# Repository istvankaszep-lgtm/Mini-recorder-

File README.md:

# Mini-recorder-

This is a recorder that can record your voice onto a sd card. Or upload music or any .mp3 format, and play it.

# Why i made this?

I made this bc
i think this is kinda cool, and harder to rout it.

# What does it have?

It has 3 button's: play, exit, record. 1 pot. meter: for selecting what to
play. It has a oled screen, a usb-c port. the sd card holder. RP2040 chip. Also a AMS1117. 
# In what did i make this?

I made this proiect with kicad.

# How to upload the firmware.

To upload the code, you gonna need to download Arduino.ide then start a new sketch, after that you gonna need to download these libraris: U8g2 (for the oled screen), and "SD" or "SdFat" ( "SD" and "SdFat" is for the SD card, you only need to download one of the two)
After you downloaded the library's just uploade the firmware from the firmware folder

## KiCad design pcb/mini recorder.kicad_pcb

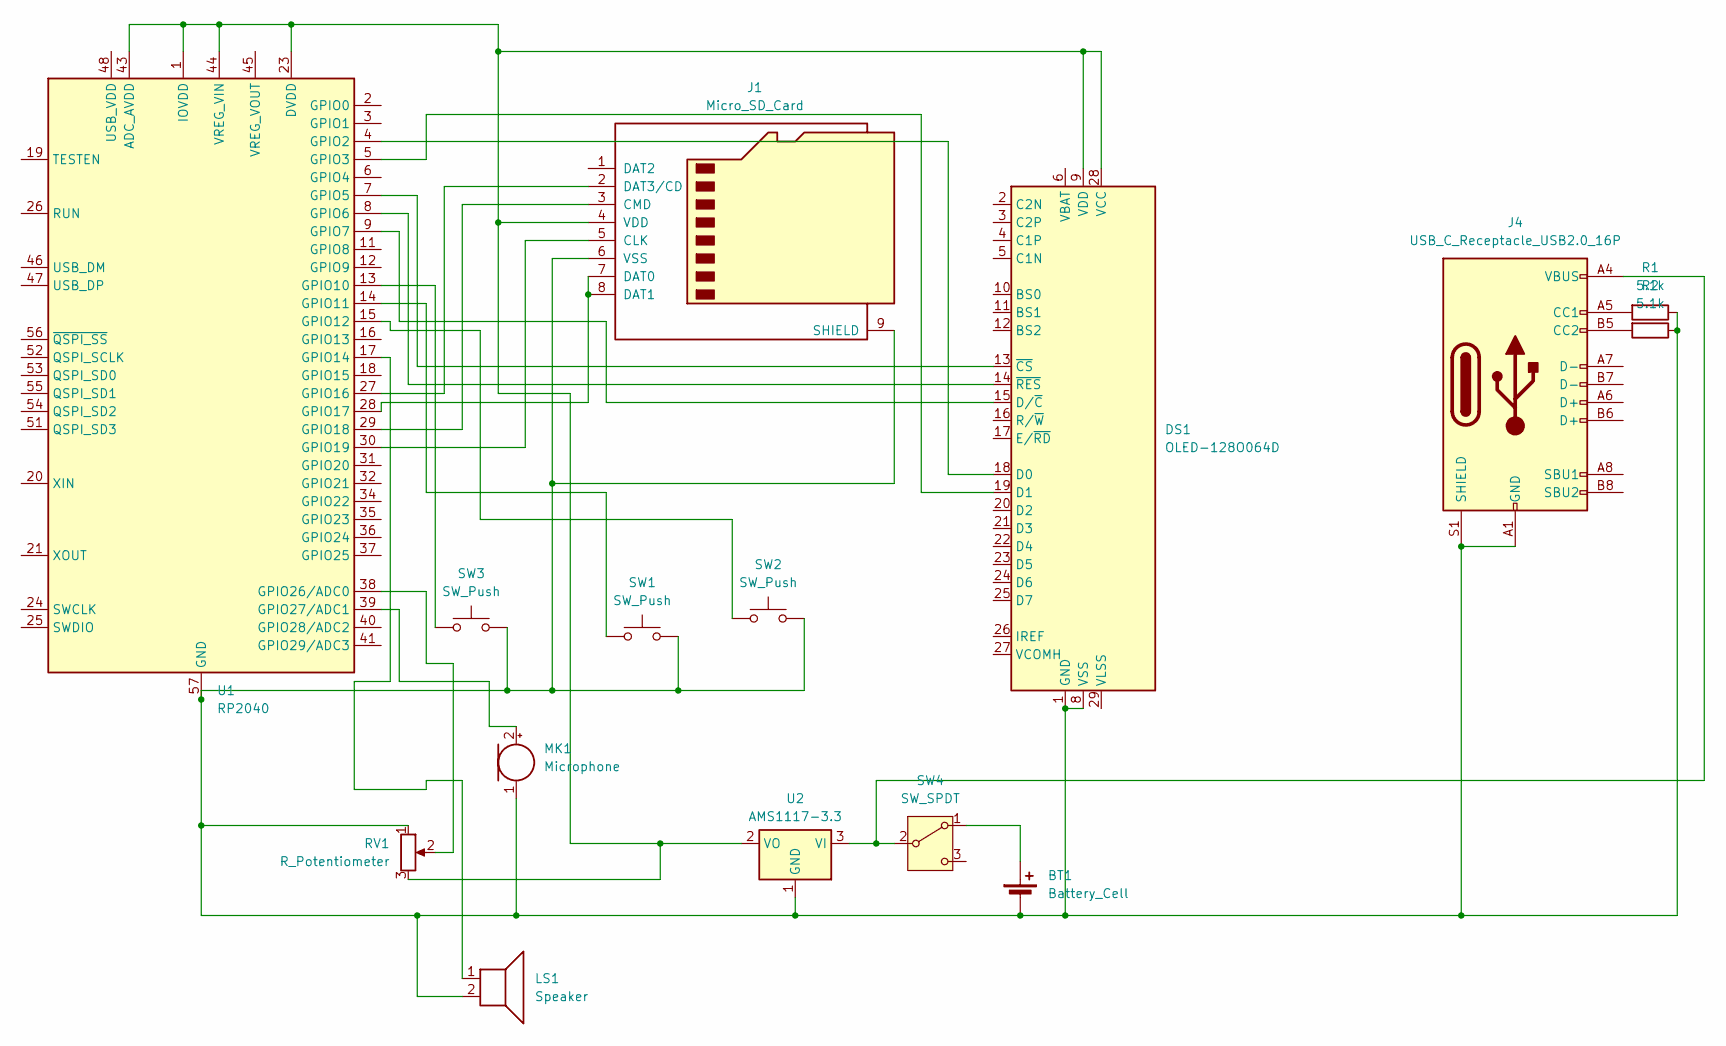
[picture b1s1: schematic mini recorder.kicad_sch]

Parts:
BT1: Battery_Cell; BatteryHolder_Bulgin_BX0036_1xC
DS1: OLED-128O064D
J1: Micro_SD_Card; microSD_HC_Hirose_DM3AT-SF-PEJM5
J4: USB_C_Receptacle_USB2.0_16P; USB_C_Receptacle_GCT_USB4085
LS1: Speaker; Buzzer_12x9.5RM7.6
MK1: Microphone; MIC_CMA-4544PF-W
R1, R2: 5.1k; R_Axial_DIN0204_L3.6mm_D1.6mm_P7.62mm_Horizontal
RV1: R_Potentiometer; Potentiometer_Alps_RK09L_Single_Vertical
SW1, SW2, SW3: SW_Push; SW_PUSH_6mm_H5mm
SW4: SW_SPDT; SW_Slide_SPDT_Straight_CK_OS102011MS2Q
U1: RP2040; QFN-56-1EP_7x7mm_P0.4mm_EP3.2x3.2mm
U2: AMS1117-3.3; SOT-223-3_TabPin2

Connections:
unnamed: BT1.1 (+), SW4.1 (A)
unnamed: BT1.2 (-), DS1.1 (GND), DS1.8 (VSS), DS1.30 (GND), J1.6 (VSS), J1.9 (SHIELD), J4.A1 (GND), J4.A12 (GND), J4.B1 (GND), J4.B12 (GND), J4.S1 (SHIELD), LS1.2, MK1.1 (-), R1.1, R2.1, RV1.1, SW1.2, SW2.2, SW3.2, U1.57 (GND), U2.1 (GND)
unnamed: DS1.18 (D0), U1.4 (GPIO2)
unnamed: DS1.19 (D1), U1.5 (GPIO3)
unnamed: DS1.15 (D/~C), U1.9 (GPIO7)
unnamed: DS1.9 (VDD), DS1.28 (VCC), J1.4 (VDD), RV1.3, U1.1 (IOVDD), U1.10 (IOVDD), U1.22 (IOVDD), U1.23 (DVDD), U1.33 (IOVDD), U1.42 (IOVDD), U1.43 (ADC_AVDD), U1.44 (VREG_VIN), U1.49 (IOVDD), U1.50 (DVDD), U2.2 (VO)
unnamed: DS1.13 (~CS), U1.7 (GPIO5)
unnamed: DS1.14 (~RES), U1.8 (GPIO6)
unnamed: J1.5 (CLK), U1.30 (GPIO19)
unnamed: J1.3 (CMD), U1.29 (GPIO18)
unnamed: J1.7 (DAT0), J1.8 (DAT1), U1.28 (GPIO17)
unnamed: J1.2 (DAT3/CD), U1.27 (GPIO16)
unnamed: J4.A5 (CC1), R1.2
unnamed: J4.B5 (CC2), R2.2
unnamed: MK1.2 (+), U1.39 (GPIO27/ADC1)
unnamed: J4.A4 (VBUS), J4.A9 (VBUS), J4.B4 (VBUS), J4.B9 (VBUS), SW4.2 (B), U2.3 (VI)
unnamed: SW3.1, U1.13 (GPIO10)
unnamed: SW1.1, U1.14 (GPIO11)
unnamed: SW2.1, U1.15 (GPIO12)
unnamed: LS1.1, U1.17 (GPIO14)
unnamed: RV1.2, U1.38 (GPIO26/ADC0)

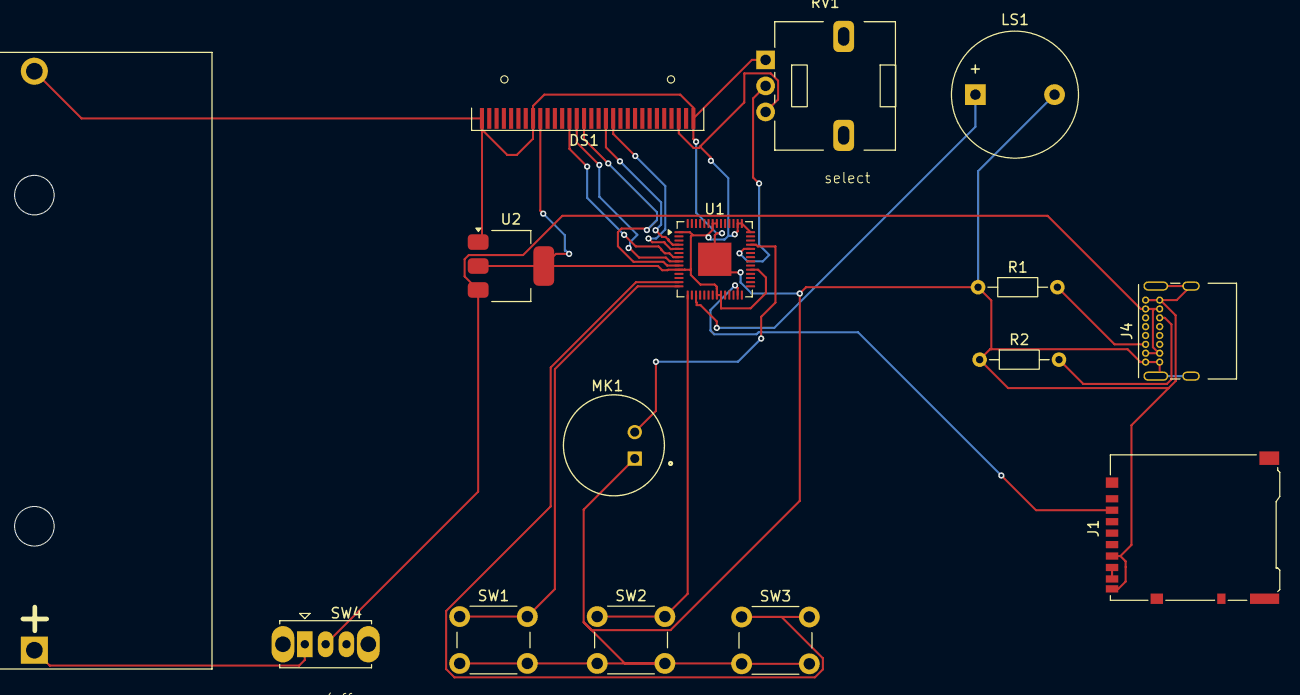
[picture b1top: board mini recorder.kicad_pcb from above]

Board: 2 copper layers, 15 parts (0 on the bottom side), 21 nets.
